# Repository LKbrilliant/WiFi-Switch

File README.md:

# WiFi-Switch 
📡 **WiFi-Switch** is a wall outlet adapter which can be controlled through the home wierless network. It can turn On/Off any device which plugs into it. This project is based on the ESP8266-01 module. Independent static-ip addresses can be use when deploying several switches around the house.

Schematics:

PCB:

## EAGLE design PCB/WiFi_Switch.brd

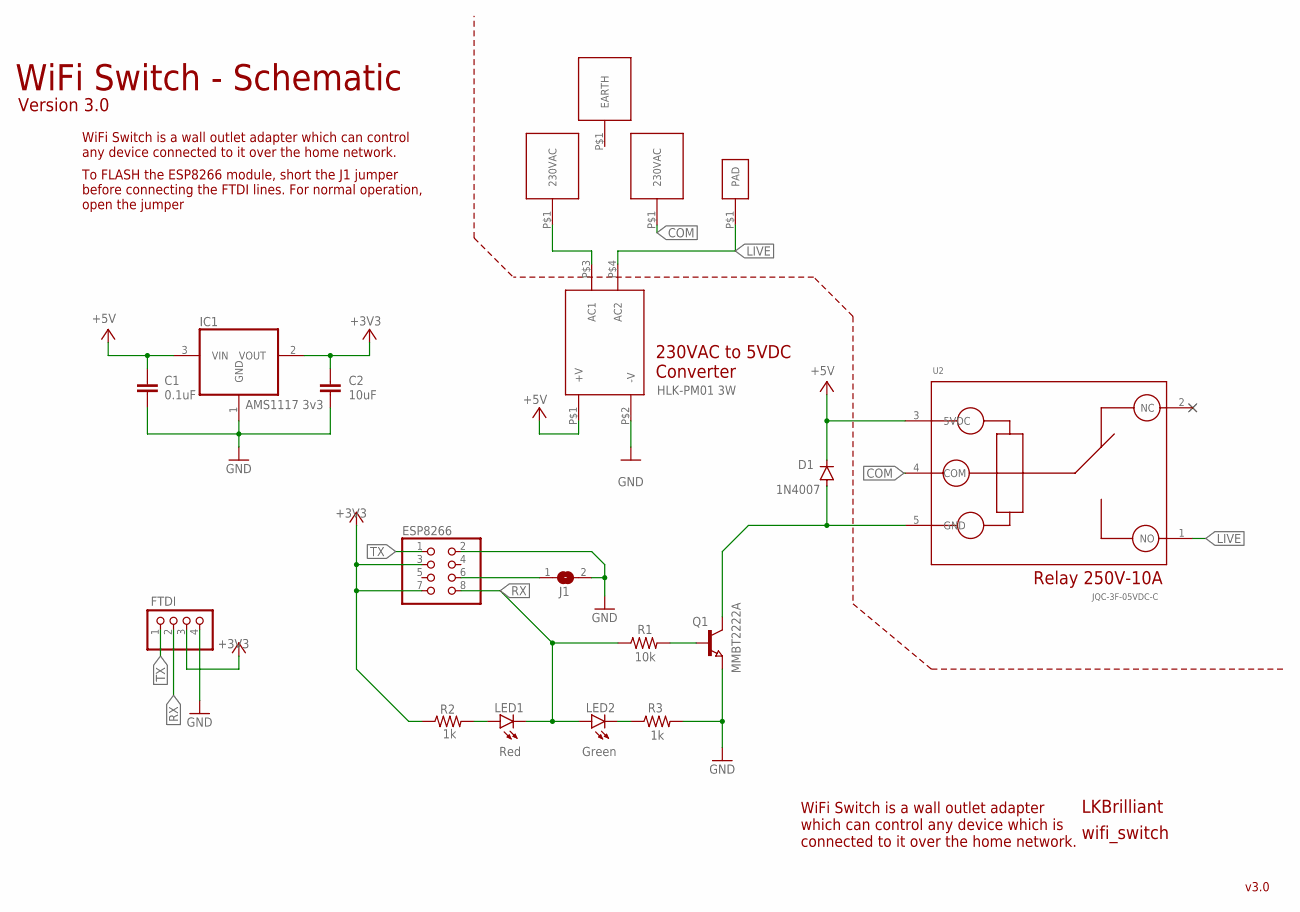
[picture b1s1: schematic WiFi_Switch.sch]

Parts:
C1: 0.1uF; C0805
C2: 10uF; C0805
D1: 1N4007; DO214AC
ESP8266: PINHD-2X4; 2X04
FTDI: PINHD-1X4; 1X04
IC1: AMS1117 3v3; SOT223
J1: SJ
L: 230VAC_PAD; 11X9_SMD_PAD
LED1: Red; CHIPLED_0603
LED2: Green; CHIPLED_0603
N: 230VAC_PAD; 11X9_SMD_PAD
Q1: MMBT2222A; SOT23
R1: 10k; R0805
R2, R3: 1k; R0805
U1: 230VAC/5VDC_CONVERTER; REG_BLOCK
U2: JQC-3F-05VDC-C; JQC-3F
U$4: EARTH_PAD; 17X8_PAD
U$5: EXT_PAD; 4X2_PAD

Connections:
+3V3: C2.1, ESP8266.3, ESP8266.7, FTDI.3, IC1.2 (VOUT), R2.1
+5V: C1.1, D1.C, IC1.3 (VIN), U1.P$1 (+V), U2.3 (5VDC)
COM: L.P$1, U2.4 (COM)
GND: C1.2, C2.2, ESP8266.2, FTDI.4, IC1.1 (GND), J1.2, Q1.2 (E), R3.2, U1.P$2 (-V)
LIVE: U1.P$4 (AC2), U2.1 (NO), U$5.P$1
unnamed: LED1.A, R2.2
unnamed: N.P$1, U1.P$3 (AC1)
unnamed: ESP8266.6, J1.1
unnamed: D1.A, Q1.3 (C), U2.5 (GND)
unnamed: LED2.C, R3.1
unnamed: Q1.1 (B), R1.2
RX: ESP8266.8, FTDI.2, LED1.C, LED2.A, R1.1
TX: ESP8266.1, FTDI.1

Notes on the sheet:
v3.0
LKBrilliant
WiFi Switch is a wall outlet adapter which can control any device which is connected to it over the home network.
230VAC to 5VDC Converter
HLK-PM01 3W
Relay 250V-10A
WiFi Switch - Schematic
Version 3.0
WiFi Switch is a wall outlet adapter which can control any device connected to it over the home network.
To FLASH the ESP8266 module, short the J1 jumper before connecting the FTDI lines. For normal operation, open the jumper

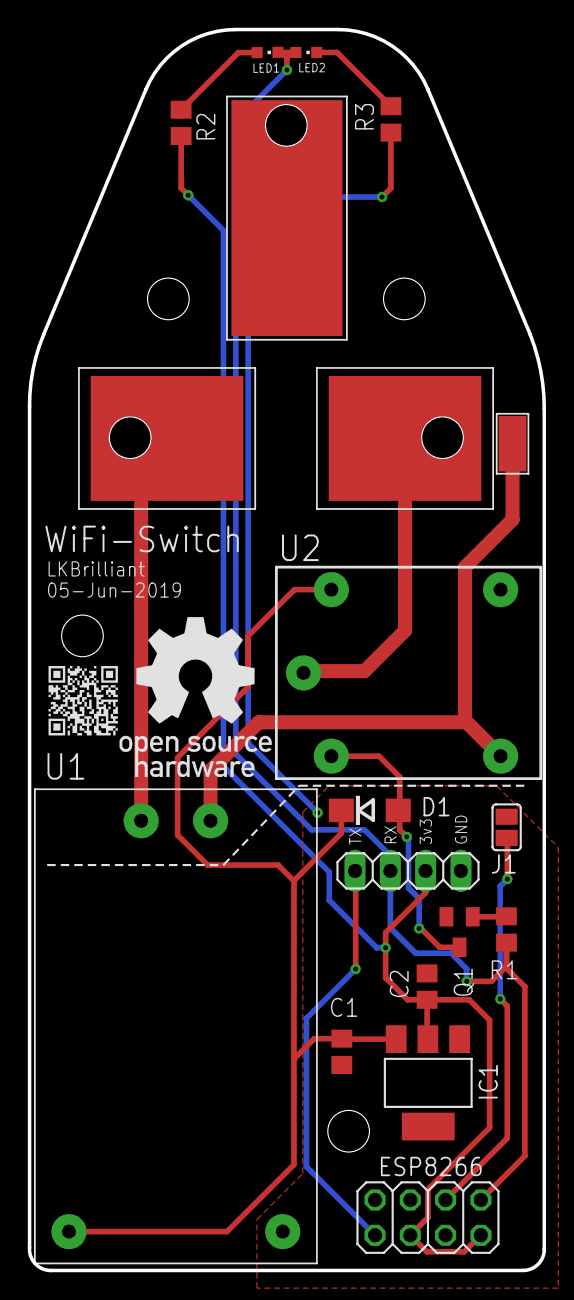
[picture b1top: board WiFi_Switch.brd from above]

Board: 2 copper layers, 37.1 x 89.4 mm, 19 parts (0 on the bottom side), 13 nets.

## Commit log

2019-05-20 initial upload
2019-05-20 rearranging
2019-05-20 deleting
2019-05-20 upload PCB data
2019-05-22 changes for v2.1
2019-05-30 minor changes
2019-05-30 Schematic info update
2019-06-02 initial source
2019-06-02 server page update
2019-06-05 version 3.0 update
2019-06-05 readme update for v3.0
2019-06-07 Add board image
2019-06-07 update the readme
2021-12-23 3D-models added
2021-12-23 License Update
